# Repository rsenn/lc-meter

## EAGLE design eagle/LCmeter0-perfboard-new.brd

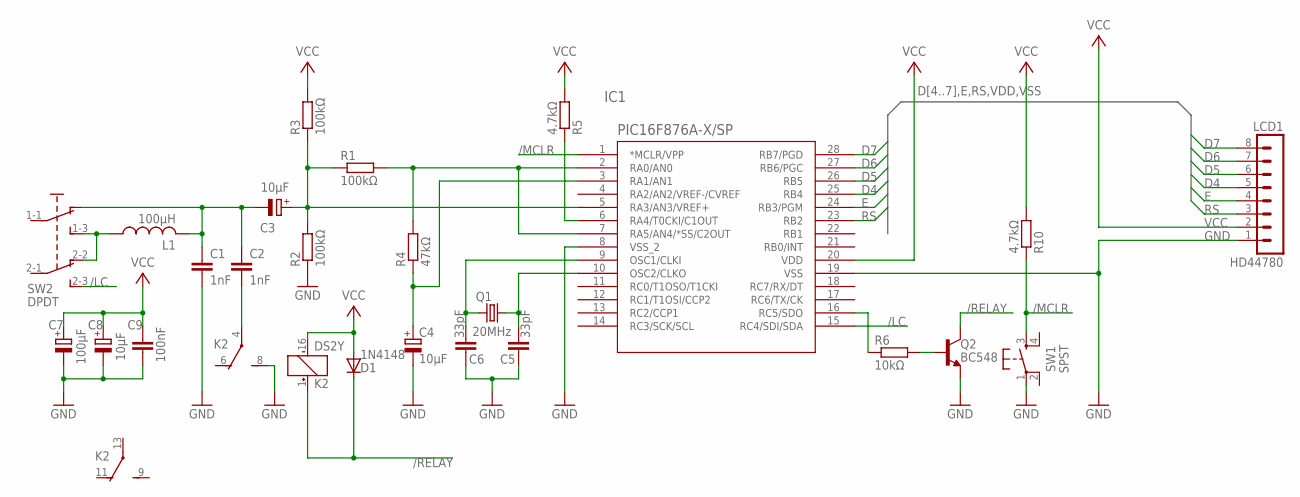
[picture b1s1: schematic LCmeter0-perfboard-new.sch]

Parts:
C1, C2: 1nF; C050-024X044
C3, C4: 10μF; E5-4
C5, C6: 33pF; C050-024X044
C7: 100μF; E2,5-6
C8: 10μF; E2,5-5
C9: 100nF; C025-024X044
D1: 1N4148; DO35-7
IC1: PIC16F876A-X/SP; DIL28-3
K2: DS2Y
L1: 100μH; 0204/5
LCD1: HD44780; MA08-1
Q1: 20MHz; HC49/S
Q2: BC548; TO92-EBC
R1: 100kΩ; 0204/7
R2, R3: 100kΩ; 0204V
R4: 47kΩ; 0204V
R5, R10: 4.7kΩ; 0207/10
R6: 10kΩ; 0204V
SW1: SPST; PB-5
SW2: DPDT

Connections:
/LC: IC1.15 (RC4/SDI/SDA), SW2.2-3
/MCLR: IC1.1 (*MCLR/VPP), R10.1, SW1.3 (S)
/RELAY: D1.C, K2.1 (+), Q2.C
A0: IC1.2 (RA0/AN0), IC1.7 (RA5/AN4/*SS/C2OUT), R1.2, R4.2
A1: C4.+, IC1.3 (RA1/AN1), R4.1
A3: C3.+, IC1.5 (RA3/AN3/VREF+), R1.1, R2.2, R3.1
A4: IC1.6 (RA4/T0CKI/C1OUT), R5.1
C2_CON: C2.2, K2.4
D4: IC1.25 (RB4), LCD1.5
D5: IC1.26 (RB5), LCD1.6
D6: IC1.27 (RB6/PGC), LCD1.7
D7: IC1.28 (RB7/PGD), LCD1.8
E: IC1.24 (RB3/PGM), LCD1.4
GND: C1.2, C4.-, C5.1, C6.1, C7.-, C8.-, C9.2, IC1.8 (VSS_2), IC1.19 (VSS), K2.8 (S), LCD1.1, Q2.E, R2.1, SW1.1
unnamed: C1.1, C2.1, C3.-, L1.2, SW2.1-2
unnamed: Q2.B, R6.2
unnamed: L1.1, SW2.1-3, SW2.2-2
OSC1: C6.2, IC1.9 (OSC1/CLKI), Q1.1
OSC2: C5.2, IC1.10 (OSC2/CLKO), Q1.2
RC5: IC1.16 (RC5/SDO), R6.1
RS: IC1.23 (RB2), LCD1.3
VCC: C7.+, C8.+, C9.1, D1.A, IC1.20 (VDD), K2.16 (-), LCD1.2, R3.2, R5.2, R10.2

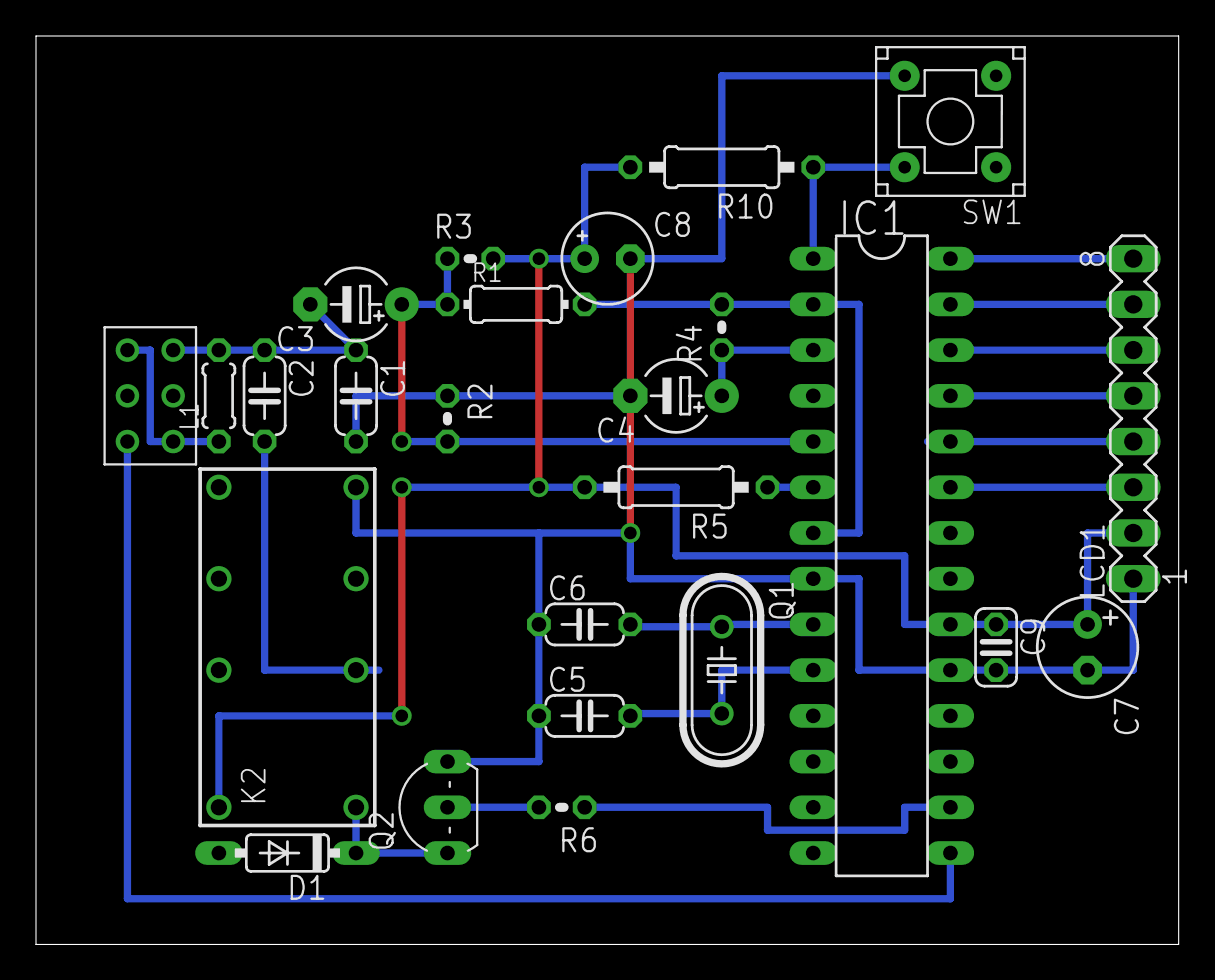
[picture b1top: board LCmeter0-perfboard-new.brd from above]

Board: 2 copper layers, 63.5 x 50.5 mm, 25 parts (0 on the bottom side), 22 nets.

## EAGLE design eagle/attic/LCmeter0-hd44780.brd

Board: 2 copper layers, 26 parts (0 on the bottom side), 24 nets.

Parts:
C1: 1nF; C050-025X075
C2: 10uF; E5-4
C3: 10uF; E5-5
C4: C025-024X044
C5: E2,5-6E
C6, C7: 22pF; C050-024X044
CCAL: 1nF; C050-025X075
D1: 1N4148; DO35-7
ICSP: FE05-1
J1: 22-27-2021-02; 6410-02
K1: DS2Y
L2: 100uH; 0204/7
LCD: FE08
Q1: HC49/S
R1, R2: 100k; 0204V
R3: 100k; 0204/7
R4: 47k; 0204V
R5: 4.7k; 0204/5
R11: 4.7k; 0204V
R12: 4.7k; 0207/10
S1: 9450-2
T1: TO92-CBE
U$2: PB-5-2; PB-5-1
U$3: PIC16F876A-X/SP-COMP-B; DIL28-3

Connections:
+5V: C4.1, C5.+, D1.C, ICSP.2, K1.1, LCD.2, R1.2, R5.2, R11.2, U$3.20
GND: C1.2, C3.-, C4.2, C5.-, C6.2, C7.2, ICSP.1, K1.4, R2.1, T1.E, U$2.2, U$3.8, U$3.19
L/C: S1.4, U$3.15
MCLR: ICSP.3, R11.1, U$2.4, U$3.1
unnamed: LCD.3, U$3.23
unnamed: LCD.4, U$3.24
unnamed: LCD.5, U$3.25
unnamed: LCD.6, U$3.26
unnamed: J1.1, S1.2
unnamed: R5.1, U$3.6
unnamed: J1.2, S1.5
unnamed: C7.1, Q1.2, U$3.10
unnamed: C6.1, Q1.1, U$3.9
unnamed: R3.1, R4.2, U$3.2, U$3.7
unnamed: R12.2, T1.B
unnamed: D1.A, K1.16, T1.C
unnamed: CCAL.2, K1.8
unnamed: C1.1, C2.+, CCAL.1, L2.2, S1.3
unnamed: L2.1, S1.1, S1.6
PGC: ICSP.4, LCD.7, U$3.27
PGD: ICSP.5, LCD.8, U$3.28
RA1: C3.+, R4.1, U$3.3
RA3: C2.-, R1.1, R2.2, R3.2, U$3.5
RELAY: R12.1, U$3.16

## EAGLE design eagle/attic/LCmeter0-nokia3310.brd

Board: 2 copper layers, 29 parts (0 on the bottom side), 27 nets.

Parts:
C1, C5: 1nF; C050-025X075
C2, C3: 10uF; E2,5-5
C4: 220nF; C050-025X075
C6, C7: 22pF; C050-025X075
CCAL: 1nF; C050-025X075
D1: 1N4148; DO35-7
K1: DS2Y
L2: 100uH; IR-2
Q1: HC49/S
R1, R3: 100k; 0204/7
R2: 100k; 0204V
R4: 47k; 0204V
R5, R12: 4.7k; 0204/7
R6, R7, R8, R9, R10: 3.3k; 0207/10
R11: 4.7k; 0204V
T1: TO92-CBE
U$1: PB-SPST; PB-5
U$2: PIC16F876A-X/SP-COMP; DIL28-3
U$3: NOKIA-3310-64X64; 1X8
U$4: S-DPDT; DPDT

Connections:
+5V: D1.C, K1.1, R1.2, R5.2, R11.2, U$2.20
GND: C1.2, C3.-, C4.2, C5.2, C6.2, C7.2, K1.4, R2.1, T1.E, U$1.4, U$2.8, U$2.19, U$3.6
L/C: U$2.21, U$4.2-3
unnamed: R6.1, U$2.12
unnamed: R7.1, U$2.13
unnamed: R8.1, U$2.14
unnamed: R9.1, U$2.15
unnamed: R10.1, U$2.16
unnamed: R5.1, U$2.6
unnamed: C5.1, R11.1, U$1.2, U$2.1
unnamed: C7.1, Q1.2, U$2.10
unnamed: C6.1, Q1.1, U$2.9
unnamed: R10.2, U$3.2
unnamed: R9.2, U$3.3
unnamed: R8.2, U$3.4
unnamed: R7.2, U$3.5
unnamed: R6.2, U$3.8
unnamed: C4.1, U$3.7
unnamed: R3.1, R4.2, U$2.2, U$2.7
unnamed: R12.2, T1.B
unnamed: D1.A, K1.16, T1.C
unnamed: CCAL.2, K1.8
unnamed: C1.1, C2.+, CCAL.1, L2.2, U$4.1-2
unnamed: L2.1, U$4.1-3, U$4.2-2
RA1: C3.+, R4.1, U$2.3
RA3: C2.-, R1.1, R2.2, R3.2, U$2.5
RELAY: R12.1, U$2.11
